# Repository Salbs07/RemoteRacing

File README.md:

# RemoteRacing
This repo contains all of the data related to the EECS 473 Remote Racing Project.

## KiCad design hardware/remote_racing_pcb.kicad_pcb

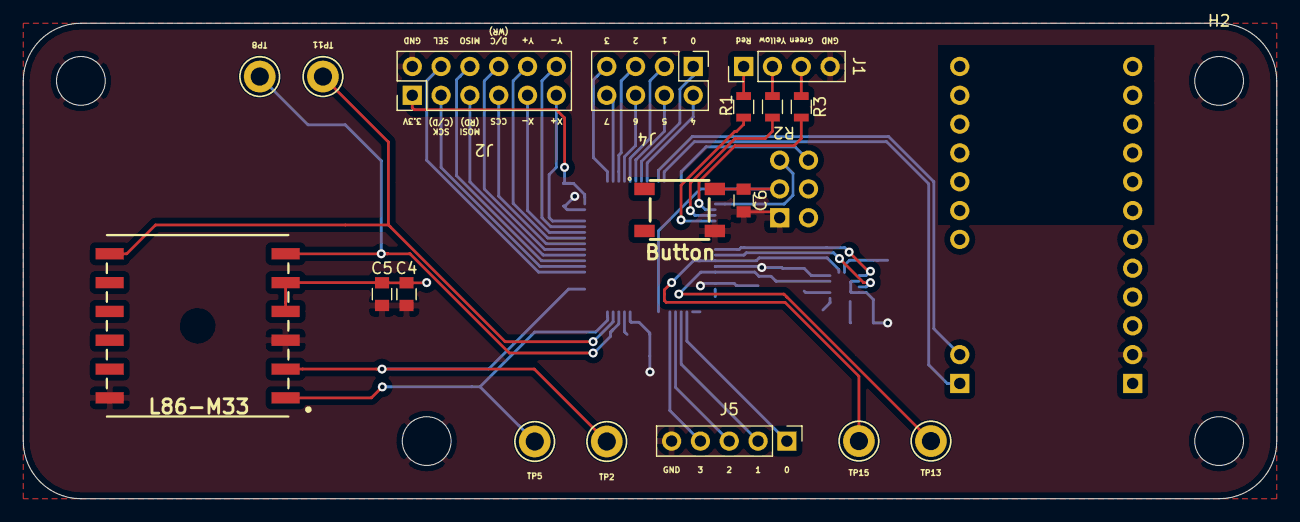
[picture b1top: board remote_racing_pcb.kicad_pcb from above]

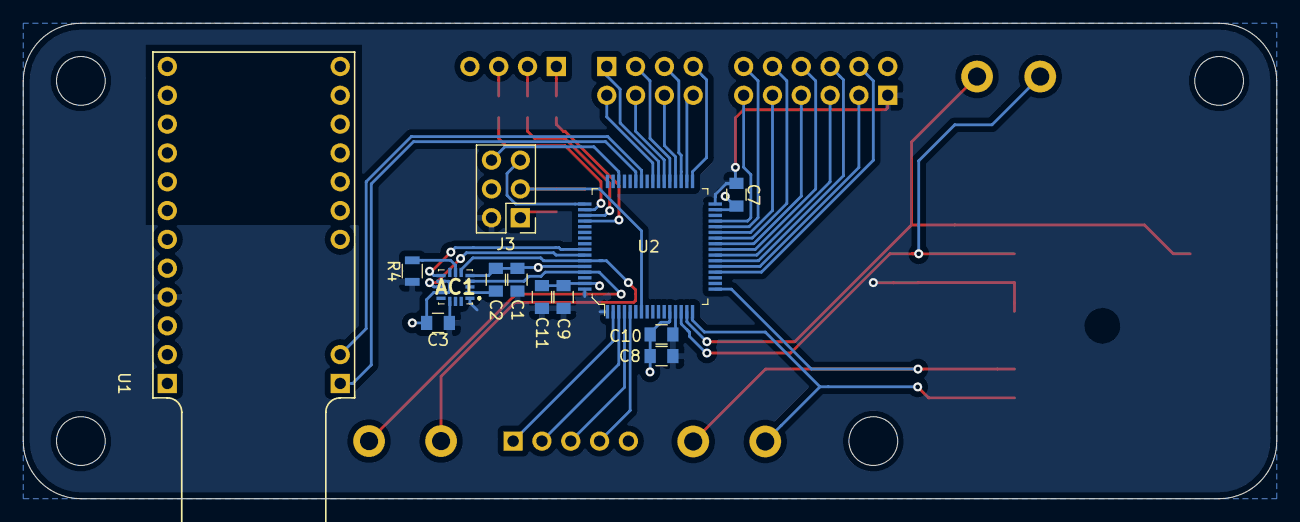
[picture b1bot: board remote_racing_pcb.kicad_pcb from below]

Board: 2 copper layers, 110.5 x 41.9 mm, 35 parts (13 on the bottom side), 45 nets.

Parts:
AC1: MMA8452QR1
C1, C2: 0.1nF; C_0805
C3, C11: 4.7uF; C_0805
C4: 10uF; C_0805
C5, C6, C7, C9: 100nF; C_0805
C8: 10nF; C_0805
C10: 1uF; C_0805
H1, H2, H3, H4: MountingHole_Pad; MountingHole_4.3mm_M4
IC1: L86-M33; L80-M39
J1: Conn_02x04_Odd_Even; Pin_Header_Straight_2x04_Pitch2.54mm
J2: Conn_01x12; Pin_Header_Straight_2x06_Pitch2.54mm
J3: Conn_02x03_Odd_Even; Pin_Header_Straight_2x03_Pitch2.54mm
J4: Conn_01x04; Pin_Header_Straight_1x04_Pitch2.54mm
J5: Conn_01x05; Pin_Header_Straight_1x05_Pitch2.54mm
R1, R2, R3: R_US; R_0805
R4: 10k; R_0805
S1: Button; SKQGAKE010
TP2, TP5, TP8, TP11, TP13, TP15: TestPoint; TestPoint_Keystone_5005-5009_Compact
U1: SparkFun_Pro_nRF52840_Mini
U2: STM32F030R8Tx; 64-LQFP_(10x10)

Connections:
+3V3: AC1.1, AC1.14, C1.1, C3.1, C4.1, C5.1, C7.1, C8.1, C9.1, C10.1, C11.1, IC1.4, IC1.5, J2.1, J3.2, R4.1, U1.4, U2.1, U2.13, U2.32, U2.64
BLE_RX: U1.15, U2.42
BLE_TX: U1.14, U2.43
GND: AC1.5, AC1.10, AC1.12, C1.2, C2.2, C3.2, C4.2, C5.2, C6.2, C7.2, C8.2, C9.2, C10.2, C11.2, H1.1, H2.1, H3.1, H4.1, IC1.3, IC1.12, J2.2, J3.1, J4.4, J5.5, S1.4, U1.2, U2.12, U2.31, U2.60, U2.63
GPS_1PPS: IC1.6, TP8.1, U2.14
GPS_FORCE_ON: IC1.7, TP11.1, U2.15
GPS_RX: IC1.1, TP5.1, U2.16
GPS_TX: IC1.2, TP2.1, U2.17
IMU_INT_1: AC1.11, U2.58
IMU_INT_2: AC1.9, U2.57
IMU_SCL: AC1.4, TP13.1, U2.61
IMU_SDA: AC1.6, TP15.1, U2.59
LCD_8BIT_0: J1.1, U2.39
LCD_8BIT_1: J1.3, U2.37
LCD_8BIT_2: J1.5, U2.35
LCD_8BIT_3: J1.7, U2.33
LCD_8BIT_4: J1.2, U2.40
LCD_8BIT_5: J1.4, U2.38
LCD_8BIT_6: J1.6, U2.36
LCD_8BIT_7: J1.8, U2.34
LCD_CCS: J2.7, U2.25
LCD_DC: J2.8, U2.24
LCD_MISO: J2.6, U2.22
LCD_MOSI: J2.5, U2.23
LCD_SCK: J2.3, U2.21
LCD_SEL: J2.4, U2.20
LCD_XM: J2.9, U2.27
LCD_XP: J2.11, U2.29
LCD_YM: J2.12, U2.28
LCD_YP: J2.10, U2.26
LED_GREEN: R3.2, U2.50
LED_RED: R1.2, U2.52
LED_YELLOW: R2.2, U2.51
NRST: C6.1, J3.3, S1.2, U2.7
unnamed: AC1.2, C2.1
unnamed: AC1.7, R4.2
unnamed: J4.1, R1.1
unnamed: J4.2, R2.1
unnamed: J4.3, R3.1
SPARE_GPIO_0: J5.1, U2.2
SPARE_GPIO_1: J5.2, U2.3
SPARE_GPIO_2: J5.3, U2.4
SPARE_GPIO_3: J5.4, U2.5
SWCLK: J3.5, U2.49
SWDIO: J3.6, U2.46

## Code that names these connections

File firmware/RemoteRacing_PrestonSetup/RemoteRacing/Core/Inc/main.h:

/* USER CODE BEGIN Header */
/**
  ******************************************************************************
  * @file           : main.h
  * @brief          : Header for main.c file.
  *                   This file contains the common defines of the application.
  ******************************************************************************
  * @attention
  *
  * <h2><center>&copy; Copyright (c) 2020 STMicroelectronics.
  * All rights reserved.</center></h2>
  *
  * This software component is licensed by ST under BSD 3-Clause license,
  * the "License"; You may not use this file except in compliance with the
  * License. You may obtain a copy of the License at:
  *                        opensource.org/licenses/BSD-3-Clause
  *
  ******************************************************************************
  */
/* USER CODE END Header */

/* Define to prevent recursive inclusion -------------------------------------*/
#ifndef __MAIN_H
#define __MAIN_H

#ifdef __cplusplus
extern "C" {
#endif

/* Includes ------------------------------------------------------------------*/
#include "stm32f0xx_hal.h"

/* Private includes ----------------------------------------------------------*/
/* USER CODE BEGIN Includes */
#include "racing_tasks.h"
/* USER CODE END Includes */

/* Exported types ------------------------------------------------------------*/
/* USER CODE BEGIN ET */
/* USER CODE END ET */

/* Exported constants --------------------------------------------------------*/
/* USER CODE BEGIN EC */

/* USER CODE END EC */

/* Exported macro ------------------------------------------------------------*/
/* USER CODE BEGIN EM */

/* USER CODE END EM */

/* Exported functions prototypes ---------------------------------------------*/
void Error_Handler(void);

/* USER CODE BEGIN EFP */

/* USER CODE END EFP */

/* Private defines -----------------------------------------------------------*/
#define SPARE_GPIO_0_Pin GPIO_PIN_13
#define SPARE_GPIO_0_GPIO_Port GPIOC
#define SPARE_GPIO_1_Pin GPIO_PIN_14
#define SPARE_GPIO_1_GPIO_Port GPIOC
#define SPARE_GPIO_2_Pin GPIO_PIN_15
#define SPARE_GPIO_2_GPIO_Port GPIOC
#define SPARE_GPIO_3_Pin GPIO_PIN_0
#define SPARE_GPIO_3_GPIO_Port GPIOF
#define GPS_1PPS_Pin GPIO_PIN_0
#define GPS_1PPS_GPIO_Port GPIOA
#define GPS_FORCE_ON_Pin GPIO_PIN_1
#define GPS_FORCE_ON_GPIO_Port GPIOA
#define SERIAL_RX_Pin GPIO_PIN_2
#define SERIAL_RX_GPIO_Port GPIOA
#define SERIAL_TX_Pin GPIO_PIN_3
#define SERIAL_TX_GPIO_Port GPIOA
#define LCD_SEL_Pin GPIO_PIN_4
#define LCD_SEL_GPIO_Port GPIOA
#define LCD_SCK_Pin GPIO_PIN_5
#define LCD_SCK_GPIO_Port GPIOA
#define LCD_MISO_Pin GPIO_PIN_6
#define LCD_MISO_GPIO_Port GPIOA
#define LCD_MOSI_Pin GPIO_PIN_7
#define LCD_MOSI_GPIO_Port GPIOA
#define LCD_DC_Pin GPIO_PIN_4
#define LCD_DC_GPIO_Port GPIOC
#define LCD_CCS_Pin GPIO_PIN_5
#define LCD_CCS_GPIO_Port GPIOC
#define LCD_YP_Pin GPIO_PIN_0
#define LCD_YP_GPIO_Port GPIOB
#define LCD_XM_Pin GPIO_PIN_1
#define LCD_XM_GPIO_Port GPIOB
#define LCD_YM_Pin GPIO_PIN_2
#define LCD_YM_GPIO_Port GPIOB
#define LCD_XP_Pin GPIO_PIN_10
#define LCD_XP_GPIO_Port GPIOB
#define LCD_8BIT_3_Pin GPIO_PIN_12
#define LCD_8BIT_3_GPIO_Port GPIOB
#define LCD_8BIT_7_Pin GPIO_PIN_13
#define LCD_8BIT_7_GPIO_Port GPIOB
#define LCD_8BIT_2_Pin GPIO_PIN_14
#define LCD_8BIT_2_GPIO_Port GPIOB
#define LCD_8BIT_6_Pin GPIO_PIN_15
#define LCD_8BIT_6_GPIO_Port GPIOB
#define LCD_8BIT_1_Pin GPIO_PIN_6
#define LCD_8BIT_1_GPIO_Port GPIOC
#define LCD_8BIT_5_Pin GPIO_PIN_7
#define LCD_8BIT_5_GPIO_Port GPIOC
#define LCD_8BIT_0_Pin GPIO_PIN_8
#define LCD_8BIT_0_GPIO_Port GPIOC
#define LCD_8BIT_4_Pin GPIO_PIN_9
#define LCD_8BIT_4_GPIO_Port GPIOC
#define GPS_RX_Pin GPIO_PIN_9
#define GPS_RX_GPIO_Port GPIOA
#define GPS_TX_Pin GPIO_PIN_10
#define GPS_TX_GPIO_Port GPIOA
#define LED_GREEN_Pin GPIO_PIN_15
#define LED_GREEN_GPIO_Port GPIOA
#define LED_YELLOW_Pin GPIO_PIN_10
#define LED_YELLOW_GPIO_Port GPIOC
#define LED_RED_Pin GPIO_PIN_11
#define LED_RED_GPIO_Port GPIOC
#define IMU_INT2_Pin GPIO_PIN_5
#define IMU_INT2_GPIO_Port GPIOB
#define IMU_INT1_Pin GPIO_PIN_6
#define IMU_INT1_GPIO_Port GPIOB
#define IMU_SDA_Pin GPIO_PIN_7
#define IMU_SDA_GPIO_Port GPIOB
#define IMU_SCL_Pin GPIO_PIN_8
#define IMU_SCL_GPIO_Port GPIOB
/* USER CODE BEGIN Private defines */
#define DEBUG_SINCE_NO_BLE // if no BLE module hooked up, this will cause UART2 to be used for debugging messages
/* USER CODE END Private defines */

#ifdef __cplusplus
}
#endif

#endif /* __MAIN_H */

/************************ (C) COPYRIGHT STMicroelectronics *****END OF FILE****/

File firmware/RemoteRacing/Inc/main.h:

/* USER CODE BEGIN Header */
/**
  ******************************************************************************
  * @file           : main.h
  * @brief          : Header for main.c file.
  *                   This file contains the common defines of the application.
  ******************************************************************************
  * @attention
  *
  * <h2><center>&copy; Copyright (c) 2020 STMicroelectronics.
  * All rights reserved.</center></h2>
  *
  * This software component is licensed by ST under BSD 3-Clause license,
  * the "License"; You may not use this file except in compliance with the
  * License. You may obtain a copy of the License at:
  *                        opensource.org/licenses/BSD-3-Clause
  *
  ******************************************************************************
  */
/* USER CODE END Header */

/* Define to prevent recursive inclusion -------------------------------------*/
#ifndef __MAIN_H
#define __MAIN_H

#ifdef __cplusplus
extern "C" {
#endif

/* Includes ------------------------------------------------------------------*/
#include "stm32f0xx_hal.h"

/* Private includes ----------------------------------------------------------*/
/* USER CODE BEGIN Includes */
#include "racing_tasks.h"
/* USER CODE END Includes */

/* Exported types ------------------------------------------------------------*/
/* USER CODE BEGIN ET */

/* USER CODE END ET */

/* Exported constants --------------------------------------------------------*/
/* USER CODE BEGIN EC */

/* USER CODE END EC */

/* Exported macro ------------------------------------------------------------*/
/* USER CODE BEGIN EM */

/* USER CODE END EM */

/* Exported functions prototypes ---------------------------------------------*/
void Error_Handler(void);

/* USER CODE BEGIN EFP */

/* USER CODE END EFP */

/* Private defines -----------------------------------------------------------*/
#define SPARE_GPIO_0_Pin GPIO_PIN_13
#define SPARE_GPIO_0_GPIO_Port GPIOC
#define SPARE_GPIO_1_Pin GPIO_PIN_14
#define SPARE_GPIO_1_GPIO_Port GPIOC
#define SPARE_GPIO_2_Pin GPIO_PIN_15
#define SPARE_GPIO_2_GPIO_Port GPIOC
#define SPARE_GPIO_3_Pin GPIO_PIN_0
#define SPARE_GPIO_3_GPIO_Port GPIOF
#define GPS_1PPS_Pin GPIO_PIN_0
#define GPS_1PPS_GPIO_Port GPIOA
#define GPS_FORCE_ON_Pin GPIO_PIN_1
#define GPS_FORCE_ON_GPIO_Port GPIOA
#define GPS_RX_Pin GPIO_PIN_2
#define GPS_RX_GPIO_Port GPIOA
#define GPS_TX_Pin GPIO_PIN_3
#define GPS_TX_GPIO_Port GPIOA
#define LCD_CS_Pin GPIO_PIN_4
#define LCD_CS_GPIO_Port GPIOA
#define LCD_DC_Pin GPIO_PIN_5
#define LCD_DC_GPIO_Port GPIOA
#define LCD_RD_Pin GPIO_PIN_7
#define LCD_RD_GPIO_Port GPIOA
#define LCD_WR_Pin GPIO_PIN_4
#define LCD_WR_GPIO_Port GPIOC
#define LCD_CCS_Pin GPIO_PIN_5
#define LCD_CCS_GPIO_Port GPIOC
#define LCD_YP_Pin GPIO_PIN_0
#define LCD_YP_GPIO_Port GPIOB
#define LCD_XM_Pin GPIO_PIN_1
#define LCD_XM_GPIO_Port GPIOB
#define LCD_YM_Pin GPIO_PIN_2
#define LCD_YM_GPIO_Port GPIOB
#define LCD_XP_Pin GPIO_PIN_10
#define LCD_XP_GPIO_Port GPIOB
#define LCD_8BIT_3_Pin GPIO_PIN_12
#define LCD_8BIT_3_GPIO_Port GPIOB
#define LCD_8BIT_7_Pin GPIO_PIN_13
#define LCD_8BIT_7_GPIO_Port GPIOB
#define LCD_8BIT_2_Pin GPIO_PIN_14
#define LCD_8BIT_2_GPIO_Port GPIOB
#define LCD_8BIT_6_Pin GPIO_PIN_15
#define LCD_8BIT_6_GPIO_Port GPIOB
#define LCD_8BIT_1_Pin GPIO_PIN_6
#define LCD_8BIT_1_GPIO_Port GPIOC
#define LCD_8BIT_5_Pin GPIO_PIN_7
#define LCD_8BIT_5_GPIO_Port GPIOC
#define LCD_8BIT_0_Pin GPIO_PIN_8
#define LCD_8BIT_0_GPIO_Port GPIOC
#define LCD_8BIT_4_Pin GPIO_PIN_9
#define LCD_8BIT_4_GPIO_Port GPIOC
#define BLE_RX_Pin GPIO_PIN_9
#define BLE_RX_GPIO_Port GPIOA
#define BLE_TX_Pin GPIO_PIN_10
#define BLE_TX_GPIO_Port GPIOA
#define LED_GREEN_Pin GPIO_PIN_15
#define LED_GREEN_GPIO_Port GPIOA
#define LED_YELLOW_Pin GPIO_PIN_10
#define LED_YELLOW_GPIO_Port GPIOC
#define LED_RED_Pin GPIO_PIN_11
#define LED_RED_GPIO_Port GPIOC
#define IMU_INT2_Pin GPIO_PIN_5
#define IMU_INT2_GPIO_Port GPIOB
#define IMU_INT1_Pin GPIO_PIN_6
#define IMU_INT1_GPIO_Port GPIOB
#define IMU_SDA_Pin GPIO_PIN_7
#define IMU_SDA_GPIO_Port GPIOB
#define IMU_SCL_Pin GPIO_PIN_8
#define IMU_SCL_GPIO_Port GPIOB
/* USER CODE BEGIN Private defines */

/* USER CODE END Private defines */

#ifdef __cplusplus
}
#endif

#endif /* __MAIN_H */

/************************ (C) COPYRIGHT STMicroelectronics *****END OF FILE****/

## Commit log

2020-10-23 Adding initial files
2020-11-02 Initial PCB Layout
2020-11-02 PCB Layout Pre-Review
2020-11-03 PCB Finished and Ordered
2020-11-03 Pcb development (#1)
    * PCB Finished and Ordered
2020-11-09 Add files via upload
    LCD interface
2020-11-09 Committing the IMU interface files
2020-11-15 initial project integration code
2020-11-18 some new files
2020-11-19 Fixed the IMU to the correct I2C interface for the PCB
2020-11-22 adding LED files
2020-11-22 GPS working on PCB
2020-11-23 BLE update
2020-11-24 racing_tasks.c cases
2020-11-25 time conversion code + race start case
2020-11-26 added app files
2020-11-28 backend files
2020-11-28 app updates
2020-11-28 almosst whoops
2020-11-28 a few fixes
2020-11-28 some more files
2020-11-28 remove unnecessary serial1 print statements and change device name
2020-11-29 backend/frontend/ble comms
2020-11-29 backend updates
2020-11-29 server fix and android compatibility files
2020-11-30 app and backend
2020-11-30 some updates for ya
2020-11-30 Added checks against GPS location lock lost
2020-11-30 Updated print_race_end_all to ensure erasure
2020-11-30 Spacing update
    Now the race results won't touch the RESULTS text!
2020-12-01 backend fixes
2020-12-01 backend
2020-12-01 fix pos_update bug
2020-12-01 a few bug fixes
2020-12-01 all the files
2020-12-01 backend change
2020-12-01 maybe bug fix
2020-12-01 another one
2020-12-01 bug fix for bug fix
2020-12-01 a new fix
2020-12-01 Added reset after race end
2020-12-02 backend changes
2020-12-08 app feature update
